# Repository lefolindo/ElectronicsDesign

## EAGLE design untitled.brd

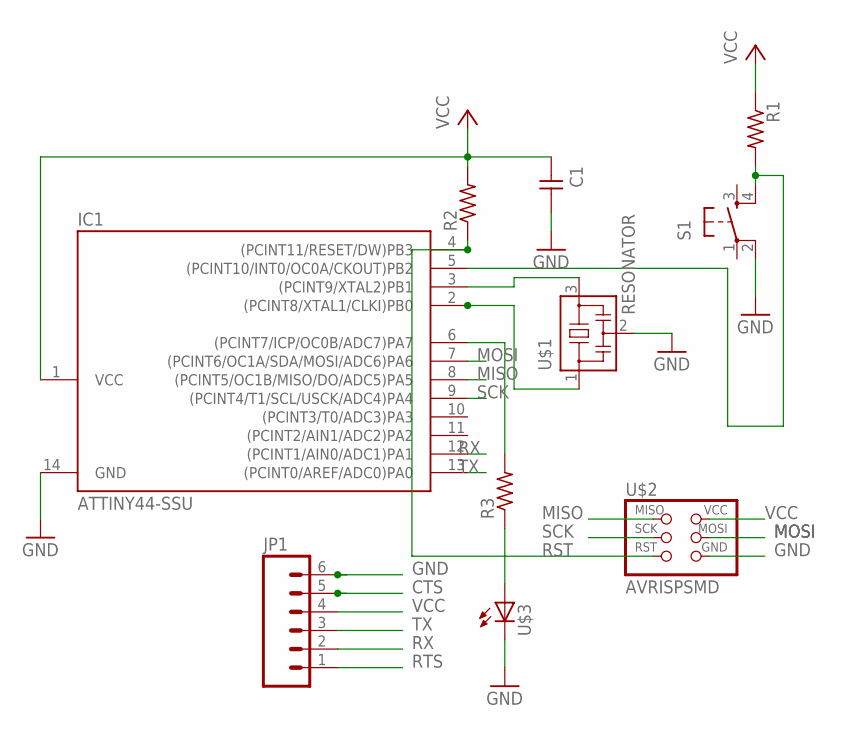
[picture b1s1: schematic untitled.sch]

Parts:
C1: UNPOLARIZED_CAPACITOR1206; 1206
IC1: ATTINY44-SSU; SOIC14
JP1: M06SMD; 1X06-SMD
R1, R2, R3: RESISTOR1206; 1206
S1: 6MM_SWITCH6MM_SWITCH; 6MM_SWITCH
U$1: RESONATOR; EFOBM
U$2: AVRISPSMD; 2X03SMD
U$3: LED1206; 1206

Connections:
CTS: JP1.5
GND: C1.2, IC1.14 (GND), JP1.6, S1.2 (P1), U$1.2, U$2.6 (GND), U$3.2 (C)
MISO: IC1.8 ((PCINT5/OC1B/MISO/DO/ADC5)PA5), U$2.1 (MISO)
MOSI: IC1.7 ((PCINT6/OC1A/SDA/MOSI/ADC6)PA6), U$2.4 (MOSI)
unnamed: IC1.2 ((PCINT8/XTAL1/CLKI)PB0), U$1.1
unnamed: IC1.3 ((PCINT9/XTAL2)PB1), U$1.3
unnamed: R3.1, U$3.1 (A)
unnamed: IC1.6 ((PCINT7/ICP/OC0B/ADC7)PA7), R3.2
unnamed: IC1.5 ((PCINT10/INT0/OC0A/CKOUT)PB2), R1.2, S1.4 (S1)
RST: IC1.4 ((PCINT11/RESET/DW)PB3), R2.1, U$2.5 (RST)
RTS: JP1.1
RX: IC1.12 ((PCINT1/AIN0/ADC1)PA1), JP1.2
SCK: IC1.9 ((PCINT4/T1/SCL/USCK/ADC4)PA4), U$2.3 (SCK)
TX: IC1.13 ((PCINT0/AREF/ADC0)PA0), JP1.3
VCC: C1.1, IC1.1 (VCC), JP1.4, R1.1, R2.2, U$2.2 (VCC)

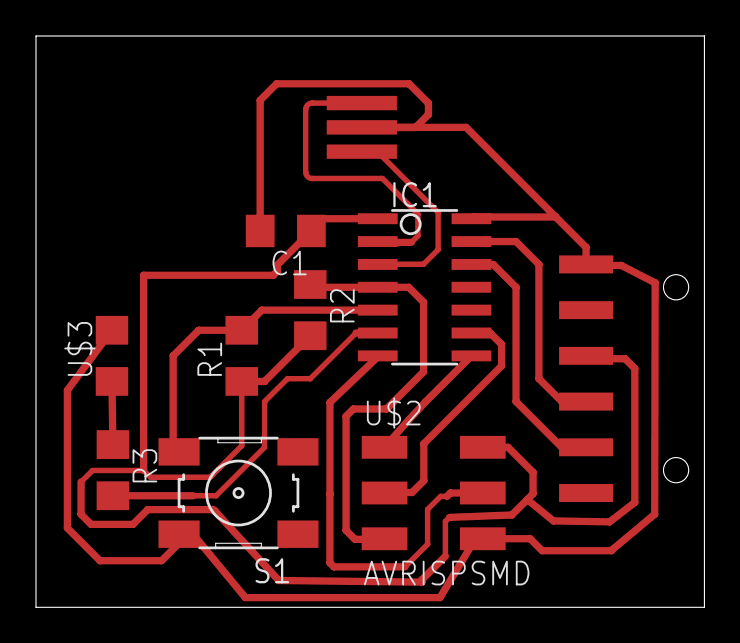
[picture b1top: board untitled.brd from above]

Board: 2 copper layers, 37.1 x 31.7 mm, 10 parts (0 on the bottom side), 13 nets.

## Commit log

2014-06-23 electronic design

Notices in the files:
parts and their libraries:
01_SparkFun: Licensing: CC v3.0 Share-Alike You are welcome to use this library for commercial purposes.
